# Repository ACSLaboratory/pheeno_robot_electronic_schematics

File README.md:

# pheeno_robot_electronic_schematics

## Pheeno Version 2.0

This is the ACSLab GitHub repository for the files relating to the electronic construction of the Pheeno robot platform. Pheeno is designed to be an inexpensive (cost of parts = $420), research-level platform for multi-robot experiments, robotics education, and outreach activities. This repository will be updated with additional modules, code, and improvements to existing modules as they are developed.

Thanks for checking out the robot!

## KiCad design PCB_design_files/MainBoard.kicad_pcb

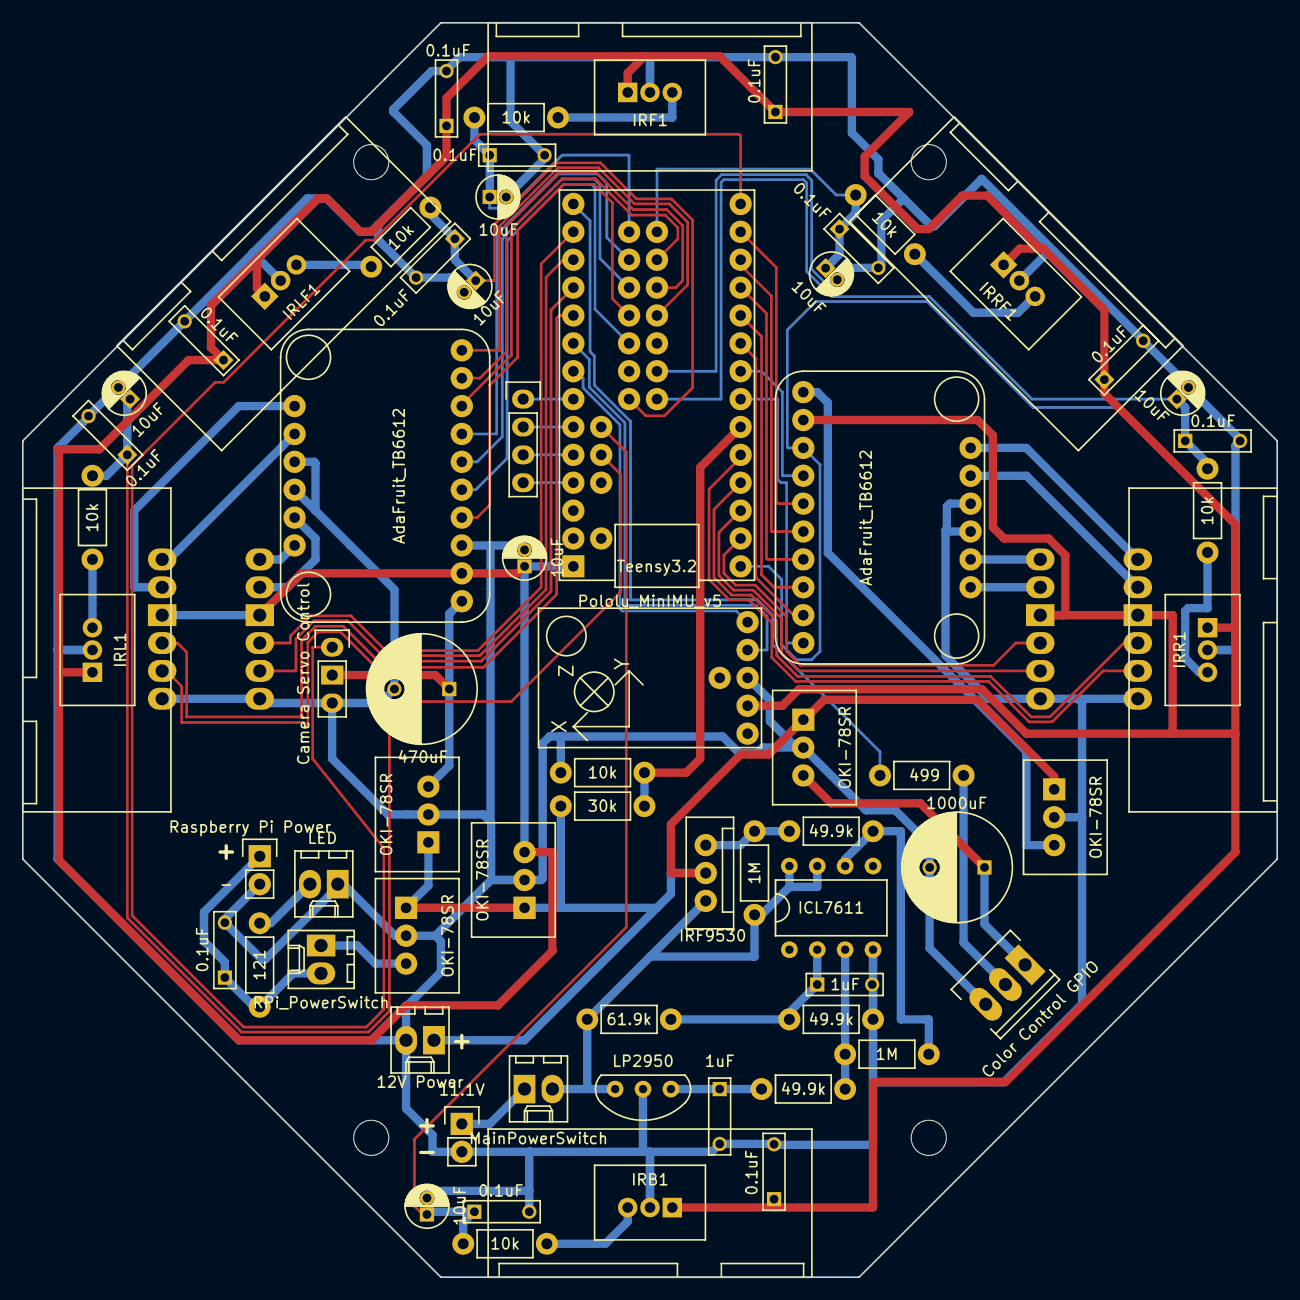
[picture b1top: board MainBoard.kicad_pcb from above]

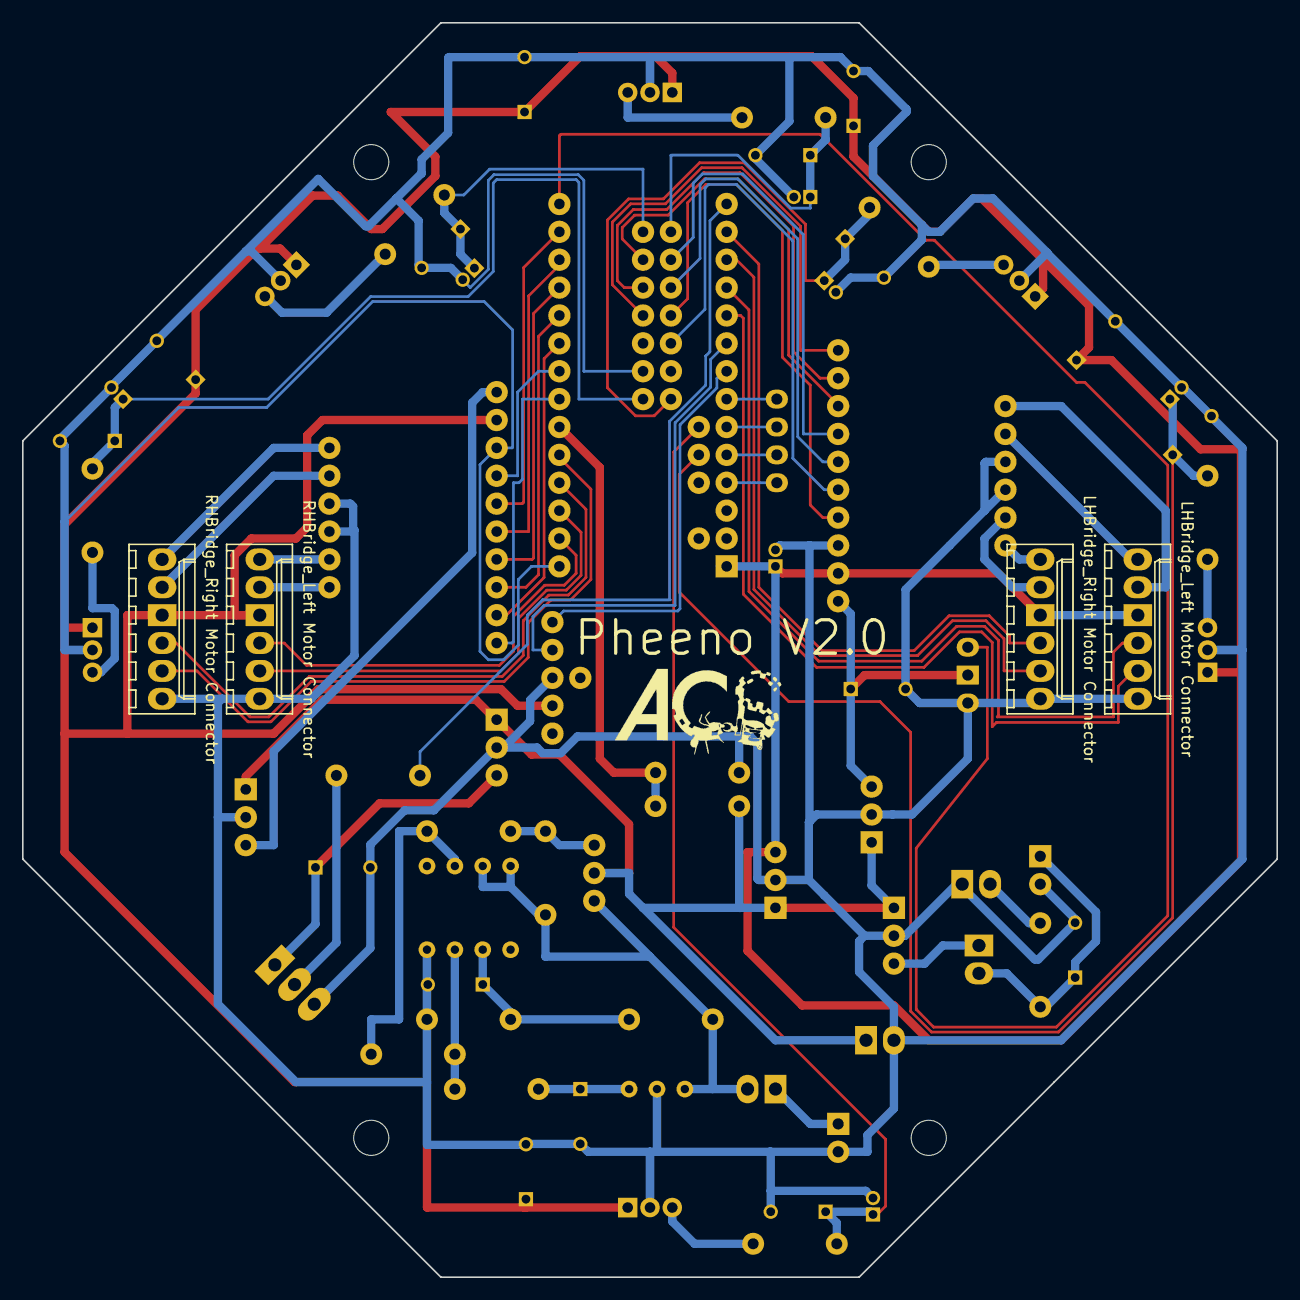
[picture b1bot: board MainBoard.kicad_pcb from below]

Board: 2 copper layers, 114.3 x 114.3 mm, 70 parts (4 on the bottom side), 68 nets.

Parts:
BT1: 11.1V; Pin_Header_Straight_1x02
C1, C2: 1uF; C_Rect_L7_W2_P5
C3, C7, C8, C9, C10, C11, C12, C13, C14, C15, C16, C17: 0.1uF; C_Rect_L7_W2_P5
C4: 1000uF; C_Radial_D10_L25_P5
C5: 470uF; C_Radial_D10_L16_P5
C6, C18, C19, C20, C21, C22, C23: 10uF; C_Radial_D4_P1.5
D1: LED; Molex_KK-6410-02_02x2.54mm_Straight
IMU1: Pololu_MinIMU_v5; Pololu_MiniIMU_v5
IRB1: GP2Y0A41SK0F
IRF1: GP2Y0A41SK0F
IRL1: GP2Y0A41SK0F
IRLF1: GP2Y0A41SK0F
IRR1: GP2Y0A41SK0F
IRRF1: GP2Y0A41SK0F
MD1, MD2: AdaFruit_TB6612
OA1: ICL7611
P1: 12V Power; Molex_KK-6410-02_02x2.54mm_Straight
P2: Raspberry Pi Power; Pin_Header_Straight_1x02
P3: Color Control GPIO; Socket_MOLEX-KK-RM2-54mm_Lock_3pin_straight
P4: Camera Servo Control; Pin_Header_Straight_1x03
P5: RHBridge_Right Motor Connector; Molex_KK-6410-06_06x2.54mm_Straight
P6: RHBridge_Left Motor Connector; Molex_KK-6410-06_06x2.54mm_Straight
P7: LHBridge_Right Motor Connector; Molex_KK-6410-06_06x2.54mm_Straight
P8: LHBridge_Left Motor Connector; Molex_KK-6410-06_06x2.54mm_Straight
P9: GPIO JUMPER; Pin_Header_Straight_1x04
Q1: IRF9530
R1: 61.9k; Resistor_Horizontal_RM7mm
R2, R3, R5: 49.9k; Resistor_Horizontal_RM7mm
R4, R6: 1M; Resistor_Horizontal_RM7mm
R7: 121; Resistor_Horizontal_RM7mm
R8: 30k; Resistor_Horizontal_RM7mm
R9, R14, R15, R16, R17, R18, R19: 10k; Resistor_Horizontal_RM7mm
R10: 499; Resistor_Horizontal_RM7mm
SW1: MainPowerSwitch; Molex_KK-6410-02_02x2.54mm_Straight
SW2: RPi_PowerSwitch; Molex_KK-6410-02_02x2.54mm_Straight
U1: LP2950
U2, U3, U4, U5, U7: OKI-78SR
U6: Teensy3.2

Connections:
/Pheeno IMU/IMU_SCL: IMU1.5, U6.21
/Pheeno IMU/IMU_SDA: IMU1.4, U6.20
/PheenoArduinoCircuit/5VCameraServo: C5.1, MD2.10, P4.2, U7.3
/PheenoArduinoCircuit/CameraControlInput: P4.1, U6.14
/PheenoArduinoCircuit/IRB_Input: C12.1, C18.1, R14.2, U6.31
/PheenoArduinoCircuit/IRF_Input: C15.1, C21.1, R17.2, U6.41
/PheenoArduinoCircuit/IRLF_Input: C14.1, C20.1, R16.2, U6.33
/PheenoArduinoCircuit/IRL_Input: C13.1, C19.1, R15.2, U6.30
/PheenoArduinoCircuit/IRRF_Input: C16.1, C22.1, R18.2, U6.40
/PheenoArduinoCircuit/IRR_Input: C17.1, C23.1, R19.2, U6.32
/PheenoArduinoCircuit/LHBridge_EncoderL_Interrupt: P8.5, U6.19
/PheenoArduinoCircuit/LHBridge_EncoderL_NoInterrupt: P8.4, U6.18
/PheenoArduinoCircuit/LHBridge_EncoderR_Interrupt: P7.5, U6.17
/PheenoArduinoCircuit/LHBridge_EncoderR_NoInterrupt: P7.4, U6.16
/PheenoArduinoCircuit/LHBridge_MotorL_IN1: MD2.3, U6.39
/PheenoArduinoCircuit/LHBridge_MotorL_IN2: MD2.2, U6.38
/PheenoArduinoCircuit/LHBridge_MotorL_PWM: MD2.1, U6.37
/PheenoArduinoCircuit/LHBridge_MotorR_IN1: MD2.5, U6.43
/PheenoArduinoCircuit/LHBridge_MotorR_IN2: MD2.6, U6.45
/PheenoArduinoCircuit/LHBridge_MotorR_PWM: MD2.7, U6.44
/PheenoArduinoCircuit/LHBridge_STBY: MD2.4, U6.42
/PheenoArduinoCircuit/RHBridge_EncoderL_Interrupt: P6.5, U6.3
/PheenoArduinoCircuit/RHBridge_EncoderL_NoInterrupt: P6.4, U6.2
/PheenoArduinoCircuit/RHBridge_EncoderR_Interrupt: P5.5, U6.5
/PheenoArduinoCircuit/RHBridge_EncoderR_NoInterrupt: P5.4, U6.4
/PheenoArduinoCircuit/RHBridge_MotorL_IN1: MD1.3, U6.10
/PheenoArduinoCircuit/RHBridge_MotorL_IN2: MD1.2, U6.9
/PheenoArduinoCircuit/RHBridge_MotorL_PWM: MD1.1, U6.7
/PheenoArduinoCircuit/RHBridge_MotorR_IN1: MD1.5, U6.12
/PheenoArduinoCircuit/RHBridge_MotorR_IN2: MD1.6, U6.13
/PheenoArduinoCircuit/RHBridge_MotorR_PWM: MD1.7, U6.8
/PheenoArduinoCircuit/RHBridge_STBY: MD1.4, U6.11
/PheenoLEDCircuit/Input5V: C4.1, P3.1, U2.3
/PheenoLEDCircuit/LEDControlInput_TeensyPin13: R10.2, U6.15
/PheenoLowVoltageCutoff/BatteryVoltageLevel_3.3V: R8.1, R9.2, U6.6
/PheenoLowVoltageCutoff/IMUCircuit5V: C6.1, C7.1, C8.1, C9.1, C10.1, C11.1, IMU1.2, IRB1.3, IRF1.3, IRL1.3, IRLF1.3, IRR1.3, IRRF1.3, MD1.9, MD2.9, P5.3, P6.3, P7.3, P8.3, U3.3, U6.28
/PheenoMotorBoardCircuit/RHBridge_Input5V_MotorPower: MD1.10, U5.3
GND: BT1.2, C1.2, C2.2, C3.2, C4.2, C5.2, C6.2, C7.2, C8.2, C9.2, C10.2, C11.2, C12.2, C13.2, C14.2, C15.2, C16.2, C17.2, C18.2, C19.2, C20.2, C21.2, C22.2, C23.2, D1.1, IMU1.3, IRB1.2, IRF1.2, IRL1.2, IRLF1.2, IRR1.2, IRRF1.2, MD1.8, MD1.13, MD1.14, MD2.8, MD2.13, MD2.14, OA1.4, P1.2, P2.2, P3.3, P4.3, P5.6, P6.6, P7.6, P8.6, R2.2, R9.1, U1.2, U2.2, U3.2, U4.2, U5.2, U6.1, U6.34, U7.2
unnamed: BT1.1, SW1.1
unnamed: C1.1, R3.2, U1.1
unnamed: C2.1, OA1.2, R1.2, R2.1
unnamed: C3.1, P2.1, R7.2, SW2.2
unnamed: D1.2, R7.1
unnamed: IRB1.1, R14.1
unnamed: IRF1.1, R17.1
unnamed: IRL1.1, R15.1
unnamed: IRLF1.1, R16.1
unnamed: IRR1.1, R19.1
unnamed: IRRF1.1, R18.1
unnamed: MD1.11, P5.1
unnamed: MD1.12, P5.2
unnamed: MD1.15, P6.1
unnamed: MD1.16, P6.2
unnamed: MD2.11, P7.1
unnamed: MD2.12, P7.2
unnamed: MD2.15, P8.1
unnamed: MD2.16, P8.2
unnamed: OA1.3, R3.1, R4.2
unnamed: OA1.6, R4.1, R5.2
unnamed: OA1.7, OA1.8, Q1.3, R1.1, R6.1, SW1.2, U1.3
unnamed: P1.1, Q1.2, R8.2, U2.1, U3.1, U4.1, U5.1, U7.1
unnamed: P3.2, R10.1
unnamed: P9.1, U6.22
unnamed: P9.2, U6.23
unnamed: P9.3, U6.24
unnamed: P9.4, U6.25
unnamed: Q1.1, R5.1, R6.2
unnamed: SW2.1, U4.3

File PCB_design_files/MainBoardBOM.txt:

"Id";"Designator";"Package";"Quantity";"Designation";"Supplier and ref";
1;"P9";"Pin_Header_Straight_1x04";1;"GPIO JUMPER";;;
2;"IRLF1,IRR1,IRB1,IRF1,IRL1,IRRF1";"GP2Y0A41SK0F";6;"GP2Y0A41SK0F";;;
3;"C17,C16,C15,C14,C13,C12,C11,C10,C9,C8,C7,C3";"C_Rect_L7_W2_P5";12;"0.1uF";;;
4;"C2,C1";"C_Rect_L7_W2_P5";2;"1uF";;;
5;"C4";"C_Radial_D10_L25_P5";1;"1000uF";;;
6;"P2";"Pin_Header_Straight_1x02";1;"Raspberry Pi Power";;;
7;"R1";"Resistor_Horizontal_RM7mm";1;"61.9k";;;
8;"R2,R3,R5";"Resistor_Horizontal_RM7mm";3;"49.9k";;;
9;"R4,R6";"Resistor_Horizontal_RM7mm";2;"1M";;;
10;"R8";"Resistor_Horizontal_RM7mm";1;"30k";;;
11;"R9,R14,R15,R16,R17,R18,R19";"Resistor_Horizontal_RM7mm";7;"10k";;;
12;"R10";"Resistor_Horizontal_RM7mm";1;"499";;;
13;"P1";"Molex_KK-6410-02_02x2.54mm_Straight";1;"12V Power";;;
14;"BT1";"Pin_Header_Straight_1x02";1;"11.1V";;;
15;"C5";"C_Radial_D10_L16_P5";1;"470uF";;;
16;"C6,C18,C19,C20,C21,C22,C23";"C_Radial_D4_P1.5";7;"10uF";;;
17;"D1";"Molex_KK-6410-02_02x2.54mm_Straight";1;"LED";;;
18;"IMU1";"Pololu_MiniIMU_v5";1;"Pololu_MinIMU_v5";;;
19;"MD1,MD2";"AdaFruit_TB6612";2;"AdaFruit_TB6612";;;
20;"OA1";"ICL7611";1;"ICL7611";;;
21;"P3";"Socket_MOLEX-KK-RM2-54mm_Lock_3pin_straight";1;"Color Control GPIO";;;
22;"P4";"Pin_Header_Straight_1x03";1;"Camera Servo Control";;;
23;"P5";"Molex_KK-6410-06_06x2.54mm_Straight";1;"RHBridge_Right Motor Connector";;;
24;"P6";"Molex_KK-6410-06_06x2.54mm_Straight";1;"RHBridge_Left Motor Connector";;;
25;"Q1";"IRF9530";1;"IRF9530";;;
26;"R7";"Resistor_Horizontal_RM7mm";1;"121";;;
27;"SW1";"Molex_KK-6410-02_02x2.54mm_Straight";1;"MainPowerSwitch";;;
28;"SW2";"Molex_KK-6410-02_02x2.54mm_Straight";1;"RPi_PowerSwitch";;;
29;"U1";"LP2950";1;"LP2950";;;
30;"U2,U3,U4,U5,U7";"OKI-78SR";5;"OKI-78SR";;;
31;"REF**,REF**,REF**,REF**";"MountingHole_3.2mm_M3";4;"MountingHole_3.2mm_M3";;;
32;"U6";"Teensy3.2";1;"Teensy3.2";;;
33;"P7";"Molex_KK-6410-06_06x2.54mm_Straight";1;"LHBridge_Right Motor Connector";;;
34;"P8";"Molex_KK-6410-06_06x2.54mm_Straight";1;"LHBridge_Left Motor Connector";;;

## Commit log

2017-05-05 Initial Commit.
2018-01-20 Removed V1 files and added V2.
2018-01-20 Added v2 files.
